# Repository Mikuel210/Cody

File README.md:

> [!IMPORTANT]
> FOR THE HORIZONS PROJECT: The correct repo is [here](https://github.com/Mikuel210/CodyFirmware). Sorry for the mistake!

---

**Cody is a robot for the next season of WRO Robomission Senior.** 

The World Robot Olympiad (WRO) is a global robotics competition. For the Robomission challenge, you have to design, build and program a robot to complete a set of challenges on a board in under 2 minutes. Cody is our attempt at making our best robot so far, and I'm designing it to be faster, more precise and more reliable than all of our previous.

## This year's challenges

1. There is a mosaic with a randomized pattern of colors at the center of the board. You have to place a block of the right color in each square of the grid to score.

2. There are blocks of "cement" of different colors on the board. You have to carry the blocks of each color to their corresponding area.

## Our solution

1. A toolhead grabs and drops blocks for the mosaic by using wheels

2. A mill picks up, carries and releases two colors of cement at a time

## How it works

- **Electronics:** I'm using an ESP32 as the microcontroller, an MPU9250 IMU for orientation and a TCS34725 color sensor for detecting the lines on the board. I'm also using an ADS1115 ADC for measuring the voltage of the battery and a PCF8575 GPIO expander.
- **Camera:** I'm using an ESP32-CAM to detect the color pattern of the mosaic.
- **Actuators:** I'm using JGB37-3530 motors for the wheels and N20 motors for the toolhead and for the mill. I'm using TB6612FNG drivers to control them.
- **Power:** I'm using a 3S 2200mAh LiPo battery for powering the robot. I'm also using a voltage regulator for powering the ESP32.
- **Structure:** I'm using 3D printed structural parts that have attachments for the components. I will be printing them out of PETG. I'm also using standard hardware such as bearings, carbon fiber rods and castor wheels.
- **Software:** I'm using odometry and a Pure Pursuit algorithm for control.

## Why I made this

My team has been using Lego Spike since we started competing, but it's starting to show its limitations. Last year, we went to the international final for the first time. Robomission had opened up to all hardwares for the first time this year, which means other teams could make faster, more precise and more reliable robots than what we could possibly do with Lego. I'm designing this robot to be faster, more precise and more reliable than our previous robots with the power of open hardware.

## PCB

## Wiring diagram

## Onshape Document

https://cad.onshape.com/documents/a1e1109ed4daddff079aebb8/w/75daa850bdae83d3a805f11b/e/0ab81b698f3d6ebcf8c57589?renderMode=1&uiState=69baba64dff3c3ac052b00d2

## Cart screenshots

> Note: I will be buying two of the carbon fiber rods above but AliExpress didn't feel like allowing me to add more than one to my cart at the moment

## BOM

> Note that the amount to buy might be higher than the amount to be used because the item is sold in bulk

|Item                            |Amount|Amount to buy|Unit price|Total price       |Link                                                                                                    |Config                         |
|--------------------------------|------|-------------|----------|------------------|--------------------------------------------------------------------------------------------------------|-------------------------------|
|PETG                            |1     |0            |0,00 €    |0,00 €            |-                                                                                                       |-                              |
|PCB                             |1     |1            |19,36 €   |19,36 €           |https://jlcpcb.com                                                                                      |-                              |
|Battery                         |2     |2            |17,50 €   |34,99 €           |https://www.amazon.es/Zeee-Bater%C3%ADa-Veh%C3%ADculos-Cuadric%C3%B3ptero-Helic%C3%B3ptero/dp/B0BYNSH6Q7|-                              |
|X Axis rods                     |2     |8            |2,17 €    |17,39 €           |https://es.aliexpress.com/item/4001063505625.html                                                       |8mm 200mm                      |
|Z Axis rods                     |2     |2            |3,29 €    |6,58 €            |https://es.aliexpress.com/item/1005006793821681.html                                                    |12x100mm 1pcs                  |
|Wheel motors                    |2     |2            |18,62 €   |37,24 €           |https://es.aliexpress.com/item/1005008730235398.html                                                    |533rpm 12V Motor x Stand       |
|N20 motors                      |4     |4            |10,47 €   |41,88 €           |https://es.aliexpress.com/item/1005009284080839.html                                                    |136x2, 272x2 without fixed seat|
|Front wheels                    |2     |2            |3,44 €    |6,87 €            |https://es.aliexpress.com/item/1005010058308140.html                                                    |49295 1pcs                     |
|Back wheels                     |2     |2            |1,69 €    |3,38 €            |https://es.aliexpress.com/item/1005005334424631.html                                                    |7.5mm 1Pcs MJ310               |
|5x10x4 Bearing                  |11    |20           |0,35 €    |6,98 €            |https://es.aliexpress.com/item/1005007668446060.html                                                    |5x10x4mm                       |
|Buzzer                          |1     |0            |0,00 €    |0,00 €            |-                                                                                                       |-                              |
|RGB LED                         |1     |0            |0,00 €    |0,00 €            |-                                                                                                       |-                              |
|Resistors                       |7     |0            |0,00 €    |0,00 €            |-                                                                                                       |-                              |
|Mechanical switch               |1     |0            |0,00 €    |0,00 €            |-                                                                                                       |-                              |
|Limit switches                  |2     |10           |0,20 €    |1,99 €            |https://es.aliexpress.com/item/1005008823539259.html                                                    |16mm Lever                     |
|TB6612FNG Motor drivers         |3     |3            |2,11 €    |6,33 €            |https://es.aliexpress.com/item/1005006983040834.html                                                    |TB6612FNG Weld                 |
|ESP32 DevKitC                   |1     |1            |5,29 €    |5,29 €            |https://es.aliexpress.com/item/1005008256121637.html                                                    |32D-Type-C-1PCS                |
|PCF8575 GPIO Expander           |1     |1            |1,63 €    |1,63 €            |https://es.aliexpress.com/item/1005002073772322.html                                                    |1PCS                           |
|ADS1115 ADC                     |1     |1            |1,59 €    |1,59 €            |https://es.aliexpress.com/item/32311656694.html                                                         |ADS1115 Blue                   |
|MPU9250 IMU                     |1     |1            |9,48 €    |9,48 €            |https://es.aliexpress.com/item/1005009033822037.html                                                    |GY-9250 original               |
|TCS34725 Color sensor           |1     |1            |3,59 €    |3,59 €            |https://es.aliexpress.com/item/1005006292597348.html                                                    |Rectangular                    |
|XT60 Connectors                 |2     |2            |0,87 €    |1,73 €            |https://es.aliexpress.com/item/1005004628891959.html                                                    |2 pairs male female            |
|JST-XH Connectors               |9     |9            |0,54 €    |4,89 €            |https://es.aliexpress.com/item/1005008638438956.html                                                    |-                              |
|12V to 6V converter             |1     |1            |2,64 €    |2,64 €            |https://es.aliexpress.com/item/1005007763337343.html                                                    |6V                             |
|ESP32-CAM                       |1     |1            |13,29 €   |13,29 €           |https://www.amazon.es/diymore-desarrollo-ESP32-CAM-MB-Bluetooth-inal%C3%A1mbrica/dp/B08X3GRK22          |-                              |
|Velcro for battery and converter|1     |1            |1,75 €    |1,75 €            |https://es.aliexpress.com/item/1005008938790125.html                                                    |Black 1M 30mm                  |
|Cable for sensors and motors    |1     |1            |2,27 €    |2,27 €            |https://es.aliexpress.com/item/1005006566120439.html                                                    |5m 22 AWG                      |
|Cable for battery               |1     |0            |0,00 €    |0,00 €            |-                                                                                                       |-                              |
|TOTAL                           |      |             |          |231,14 € ($267,79)|                                                                                                        |                               |

---

Made with ❤️ for Blueprint thanks to Hack Club

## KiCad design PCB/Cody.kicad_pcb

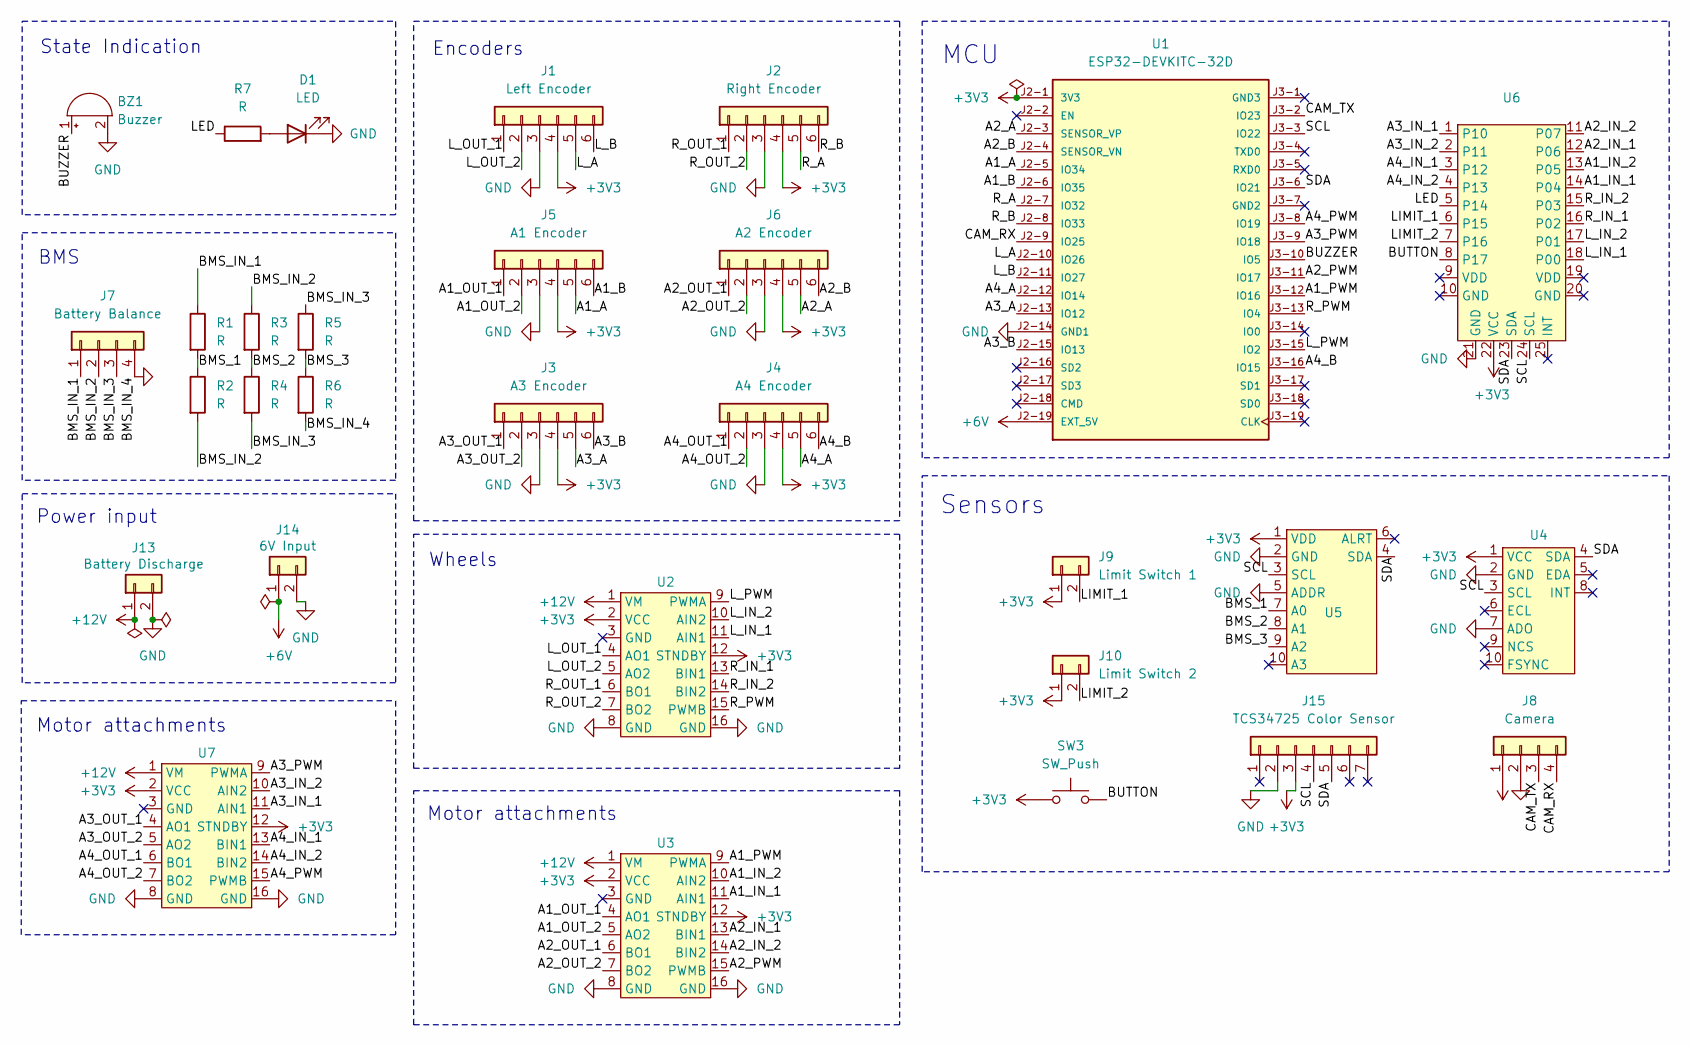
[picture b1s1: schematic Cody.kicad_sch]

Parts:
BZ1: Buzzer; Buzzer_12x9.5RM7.6
D1: LED; LED_D3.0mm
J1: Left Encoder; JST_XH_B6B-XH-A_1x06_P2.50mm_Vertical
J2: Right Encoder; JST_XH_B6B-XH-A_1x06_P2.50mm_Vertical
J3: A3 Encoder; JST_XH_B6B-XH-A_1x06_P2.50mm_Vertical
J4: A4 Encoder; JST_XH_B6B-XH-A_1x06_P2.50mm_Vertical
J5: A1 Encoder; JST_XH_B6B-XH-A_1x06_P2.50mm_Vertical
J6: A2 Encoder; JST_XH_B6B-XH-A_1x06_P2.50mm_Vertical
J7: Battery Balance; JST_XH_B4B-XH-A_1x04_P2.50mm_Vertical
J8: Camera; JST_XH_B4B-XH-A_1x04_P2.50mm_Vertical
J9: Limit Switch 1; JST_XH_B2B-XH-A_1x02_P2.50mm_Vertical
J10: Limit Switch 2; JST_XH_B2B-XH-A_1x02_P2.50mm_Vertical
J13: Battery Discharge; AMASS_XT60-M_1x02_P7.20mm_Vertical
J14: 6V Input; AMASS_XT60-M_1x02_P7.20mm_Vertical
J15: TCS34725 Color Sensor; JST_XH_B7B-XH-A_1x07_P2.50mm_Vertical
R1, R2, R3, R4, R5, R6, R7: R; R_Axial_DIN0207_L6.3mm_D2.5mm_P7.62mm_Horizontal
SW3: SW_Push; SW_Cherry_MX_1.00u_PCB
U1: ESP32-DEVKITC-32D; PARTREV V4; DigiKey_Part_Number 1965-1000-ND
U2, U3, U7: TB6612FNG
U4: GY-9250
U5: ADS1115
U6: PCF8575

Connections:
+3V3: J1.4, J2.4, J3.4, J4.4, J5.4, J6.4, J9.1, J10.1, J15.3, SW3.1, U1.J2-1 (3V3), U2.2 (VCC), U2.12 (STNDBY), U3.2 (VCC), U3.12 (STNDBY), U4.1 (VCC), U5.1 (VDD), U6.22 (VCC), U7.2 (VCC), U7.12 (STNDBY)
+6V: J8.1, J14.1, U1.J2-19 (EXT_5V)
+12V: J13.1, U2.1 (VM), U3.1 (VM), U7.1 (VM)
/A1_A: J5.5, U1.J2-5 (IO34)
/A1_B: J5.6, U1.J2-6 (IO35)
/A1_IN_1: U3.11 (AIN1), U6.14 (P04)
/A1_IN_2: U3.10 (AIN2), U6.13 (P05)
/A1_OUT_1: J5.1, U3.4 (AO1)
/A1_OUT_2: J5.2, U3.5 (AO2)
/A1_PWM: U1.J3-12 (IO16), U3.9 (PWMA)
/A2_A: J6.5, U1.J2-3 (SENSOR_VP)
/A2_B: J6.6, U1.J2-4 (SENSOR_VN)
/A2_IN_1: U3.13 (BIN1), U6.12 (P06)
/A2_IN_2: U3.14 (BIN2), U6.11 (P07)
/A2_OUT_1: J6.1, U3.6 (BO1)
/A2_OUT_2: J6.2, U3.7 (BO2)
/A2_PWM: U1.J3-11 (IO17), U3.15 (PWMB)
/A3_A: J3.5, U1.J2-13 (IO12)
/A3_B: J3.6, U1.J2-15 (IO13)
/A3_IN_1: U6.1 (P10), U7.11 (AIN1)
/A3_IN_2: U6.2 (P11), U7.10 (AIN2)
/A3_OUT_1: J3.1, U7.4 (AO1)
/A3_OUT_2: J3.2, U7.5 (AO2)
/A3_PWM: U1.J3-9 (IO18), U7.9 (PWMA)
/A4_A: J4.5, U1.J2-12 (IO14)
/A4_B: J4.6, U1.J3-16 (IO15)
/A4_IN_1: U6.3 (P12), U7.13 (BIN1)
/A4_IN_2: U6.4 (P13), U7.14 (BIN2)
/A4_OUT_1: J4.1, U7.6 (BO1)
/A4_OUT_2: J4.2, U7.7 (BO2)
/A4_PWM: U1.J3-8 (IO19), U7.15 (PWMB)
/BMS_1: R1.2, R2.1, U5.7 (A0)
/BMS_2: R3.2, R4.1, U5.8 (A1)
/BMS_3: R5.2, R6.1, U5.9 (A2)
/BMS_IN_1: J7.1, R1.1
/BMS_IN_2: J7.2, R2.2, R3.1
/BMS_IN_3: J7.3, R4.2, R5.1
/BUTTON: SW3.2, U6.8 (P17)
/BUZZER: BZ1.1 (+), U1.J3-10 (IO5)
/CAM_RX: J8.4, U1.J2-9 (IO25)
/CAM_TX: J8.3, U1.J3-2 (IO23)
/LED: R7.1, U6.5 (P14)
/LIMIT_1: J9.2, U6.6 (P15)
/LIMIT_2: J10.2, U6.7 (P16)
/L_A: J1.5, U1.J2-10 (IO26)
/L_B: J1.6, U1.J2-11 (IO27)
/L_IN_1: U2.11 (AIN1), U6.18 (P00)
/L_IN_2: U2.10 (AIN2), U6.17 (P01)
/L_OUT_1: J1.1, U2.4 (AO1)
/L_OUT_2: J1.2, U2.5 (AO2)
/L_PWM: U1.J3-15 (IO2), U2.9 (PWMA)
/R_A: J2.5, U1.J2-7 (IO32)
/R_B: J2.6, U1.J2-8 (IO33)
/R_IN_1: U2.13 (BIN1), U6.16 (P02)
/R_IN_2: U2.14 (BIN2), U6.15 (P03)
/R_OUT_1: J2.1, U2.6 (BO1)
/R_OUT_2: J2.2, U2.7 (BO2)
/R_PWM: U1.J3-13 (IO4), U2.15 (PWMB)
/SCL: J15.4, U1.J3-3 (IO22), U4.3 (SCL), U5.3 (SCL), U6.24 (SCL)
/SDA: J15.5, U1.J3-6 (IO21), U4.4 (SDA), U5.4 (SDA), U6.23 (SDA)
GND: BZ1.2 (-), D1.1 (K), J1.3, J2.3, J3.3, J4.3, J5.3, J6.3, J7.4, J8.2, J13.2, J14.2, J15.2, R6.2, U1.J2-14 (GND1), U2.8 (GND), U2.16 (GND), U3.8 (GND), U3.16 (GND), U4.2 (GND), U4.7 (ADO), U5.2 (GND), U5.5 (ADDR), U6.21 (GND), U7.8 (GND), U7.16 (GND)
unnamed: D1.2 (A), R7.2

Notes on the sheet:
Sensors
Encoders
Power input
Wheels
Motor attachments
BMS
MCU
State Indication

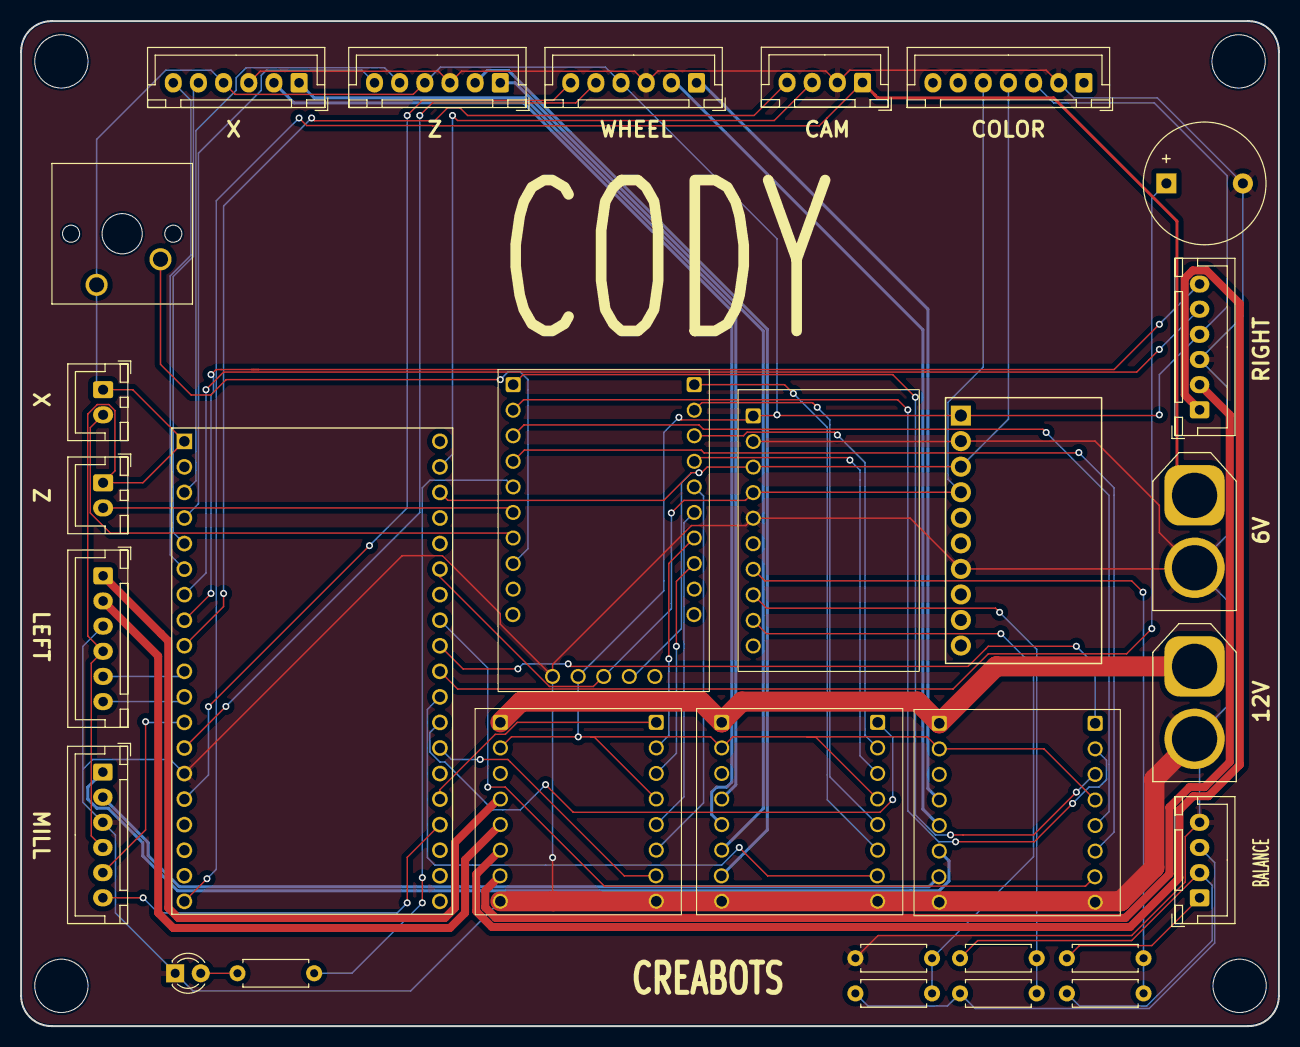
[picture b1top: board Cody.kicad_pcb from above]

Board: 2 copper layers, 125.0 x 99.9 mm, 30 parts (0 on the bottom side), 62 nets.

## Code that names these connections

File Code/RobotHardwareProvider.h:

#pragma once
#include "IHardwareProvider.h"
#include "GPIO.h"
#include "Cody.h"
#include <Arduino.h>
#include <Wire.h>

// PWM
#define L_PWM 2
#define R_PWM 4
#define A1_PWM 16 // X
#define A2_PWM 17 // Z
#define A3_PWM 18 // Wheels
#define A4_PWM 19 // Mill

// Direction
#define L_IN_1 0
#define L_IN_2 1
#define R_IN_1 2
#define R_IN_2 3
#define A1_IN_1 4
#define A1_IN_2 5
#define A2_IN_1 6
#define A2_IN_2 7
#define A3_IN_1 8
#define A3_IN_2 9
#define A4_IN_1 10
#define A4_IN_2 11

// State indication
#define LED 12
#define BUZZER 5

// PWM to PPM
#define WHEELS_MAX_PPM 36240

class RobotHardwareProvider : public IHardwareProvider {
  public:
    void initialize() override {
      pinMode(L_PWM, OUTPUT);
      pinMode(R_PWM, OUTPUT);
      pinMode(A1_PWM, OUTPUT);
      pinMode(A2_PWM, OUTPUT);
      pinMode(A3_PWM, OUTPUT);
      pinMode(A4_PWM, OUTPUT);
      pinMode(BUZZER, OUTPUT);
    }

    void move(NavigationData navigationData) override {
      //navigationData.leftMotor.pwm *= 0.9;
      moveMotor(navigationData.leftMotor, L_IN_1, L_IN_2, L_PWM);
      moveMotor(navigationData.rightMotor, R_IN_1, R_IN_2, R_PWM);
    }

    void moveToolhead(ToolheadData toolheadData) override {
      moveMotor(toolheadData.xAxisMotor, A1_IN_1, A1_IN_2, A1_PWM);
      moveMotor(toolheadData.zAxisMotor, A2_IN_1, A2_IN_2, A2_PWM);
    }

    void moveWheels(WheelsData wheelsData) override {
      moveMotor(wheelsData.wheelsMotor, A3_IN_1, A3_IN_2, A3_PWM);
    }

    void moveMill(MillData millData) override {
      moveMotor(millData.millMotor, A4_IN_1, A4_IN_2, A4_PWM);
    }

    void writeLed(uint8_t value) override {
      GPIO::digitalWrite(LED, value);
    }

    void toneBuzzer(unsigned int frequency, unsigned long duration = 0) override {
      if (duration == 0) tone(BUZZER, frequency);
      else tone(BUZZER, frequency, duration);
    }

    void noToneBuzzer() override {
      noTone(BUZZER);
    }

  private:
    void moveMotor(MotorData motorData, unsigned int in1, unsigned int in2, unsigned int pwm) {
      if (motorData.forwards) {
        GPIO::digitalWrite(in1, HIGH);
        GPIO::digitalWrite(in2, LOW);
      } else {
        GPIO::digitalWrite(in1, LOW);
        GPIO::digitalWrite(in2, HIGH);
      }

      analogWrite(pwm, motorData.pwm);
    }
};

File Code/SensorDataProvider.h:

#pragma once
#include "IDataProvider.h"
#include "GPIO.h"
#include "TCS34725.h"
#include <Arduino.h>
#include <Wire.h>
#include <ESP32Encoder.h>
#include <FastIMU.h>
#include <ADS1115_WE.h>
#include <Wire.h>

#define IMU_ADDRESS 0x68
#define ADS_ADDRESS 0x48
#define G 9.807
#define DEG2RAD 0.01745329251f

// Encoders
#define L_A 26
#define L_B 27
#define R_A 32
#define R_B 33
#define A1_A 34
#define A1_B 35
#define A2_A 36
#define A2_B 39
#define A3_A 12
#define A3_B 13
#define A4_A 14
#define A4_B 15

// Switches
#define LIMIT_1 13
#define LIMIT_2 14
#define BUTTON 15

// Sensors
ADS1115_WE ADS = ADS1115_WE(ADS_ADDRESS);
TCS34725 TCS;

class SensorDataProvider : public IDataProvider {
  public:
    void initialize() override {
      // Initialize IMU
      Wire.begin();
      Wire.setClock(400000);

      IMU.setIMUGeometry(7);
      int error = IMU.init({ 0 }, IMU_ADDRESS);

      if (error != 0) {
        Serial.print("Error initializing IMU: ");
        Serial.println(error);
      }

      // Initialize ADS1115
      Wire.begin();

      while (!ADS.init()) {
        Serial.println("Initializing ADS");
        delay(1);
      }

      ADS.setVoltageRange_mV(ADS1115_RANGE_6144);
      ADS.setMeasureMode(ADS1115_CONTINUOUS);

      // Initialize TCS34725
      /*
      while (!TCS.attach(Wire)) {
        Serial.println("Initializing TCS");
        delay(1);
      }

      TCS.integrationTime(1000.0 / HZ);
      TCS.gain(TCS34725::Gain::X01);*/

      // Initialize PCF8575
      GPIO::initialize();
      
      // Initialize encoders
      leftEncoder.attachHalfQuad(L_A, L_B);
      leftEncoder.setCount(0);
      rightEncoder.attachHalfQuad(R_A, R_B);
      rightEncoder.setCount(0);
      xEncoder.attachHalfQuad(A1_A, A1_B);
      xEncoder.setCount(0);
      zEncoder.attachHalfQuad(A2_A, A2_B);
      zEncoder.setCount(0);
      wheelsEncoder.attachHalfQuad(A3_A, A3_B);
      wheelsEncoder.setCount(0);
      millEncoder.attachHalfQuad(A4_A, A4_B);
      millEncoder.setCount(0);
    }

    SensorData getData() override {
      SensorData data;

      // Get IMU data
      /*IMU.update();
      data.acceleration = readAccelerometer();
      data.gyroscope = readGyroscope();
      data.magnetometer = readMagnetometer();*/

      // Get wheel pulses
      data.leftPulses = leftEncoder.getCount();
      data.rightPulses = -rightEncoder.getCount();
      data.xAxisPulses = xEncoder.getCount();
      data.zAxisPulses = zEncoder.getCount();
      data.wheelsPulses = wheelsEncoder.getCount();
      data.millPulses = millEncoder.getCount();

      // Get color sensor
      /*if (TCS.available()) {
          TCS34725::Color color = TCS.color();
          data.colorData = ColorData(color.r, color.g, color.b);
      }*/

      // Get BMS
      data.bms1 = readVoltage(ADS1115_COMP_0_GND);
      data.bms2 = readVoltage(ADS1115_COMP_1_GND);
      data.bms3 = readVoltage(ADS1115_COMP_3_GND);

      // Get switches
      data.xLimit = GPIO::digitalRead(LIMIT_2) == 1;
      data.zLimit = GPIO::digitalRead(LIMIT_1) == 1;
      data.button = GPIO::digitalRead(BUTTON) == 1;

      return data;
    }

  private:
    // Encoders
    ESP32Encoder leftEncoder;
    ESP32Encoder rightEncoder;
    ESP32Encoder xEncoder;
    ESP32Encoder zEncoder;
    ESP32Encoder wheelsEncoder;
    ESP32Encoder millEncoder;

    // Orientation
    MPU9250 IMU;
    AccelData accelData;
    GyroData gyroData;
    MagData magData;

    Vector3 readAccelerometer() {
      Vector3 acceleration;
      IMU.getAccel(&accelData);
      acceleration.x = accelData.accelX * G;
      acceleration.y = accelData.accelY * G;
      acceleration.z = accelData.accelZ * G;

      return acceleration;
    }

    Vector3 readGyroscope() {
      Vector3 gyroscope;
      IMU.getGyro(&gyroData);
      gyroscope.x = gyroData.gyroX * DEG2RAD;
      gyroscope.y = gyroData.gyroY * DEG2RAD;
      gyroscope.z = gyroData.gyroZ * DEG2RAD;

      return gyroscope;
    }

    Vector3 readMagnetometer() {
      Vector3 magnetometer;
      IMU.getMag(&magData);
      magnetometer.x = magData.magX;
      magnetometer.y = magData.magY;
      magnetometer.z = magData.magZ;

      return magnetometer;
    }

    double readVoltage(ADS1115_MUX channel) {
      ADS.setCompareChannels(channel);
      return ADS.getResult_V();
    }
};

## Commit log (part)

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2025-12-20 20-12-2025
2025-12-29 29-12-2025
2026-01-23 23-01-2026
2026-03-11 11-03-2026
2026-03-12 12-03-2026
2026-03-18 18-03-2026
2026-03-21 21-03-2026
2026-03-27 27-03-2026
2026-03-30 Half-working Pure Pursuit
2026-03-31 30-03-2026
2026-04-02 refactor: Abstracted Pure Pursuit
2026-04-08 Switch computers
2026-05-01 Added wheels and robot hardware
2026-05-07 Added sensors and state indication
2026-05-07 Added toolhead homing
2026-05-15 Added mill
2026-05-15 Link code
2026-05-22 Integrated testing
2026-05-28 Working GPIO expander
2026-06-26 Fix images again
